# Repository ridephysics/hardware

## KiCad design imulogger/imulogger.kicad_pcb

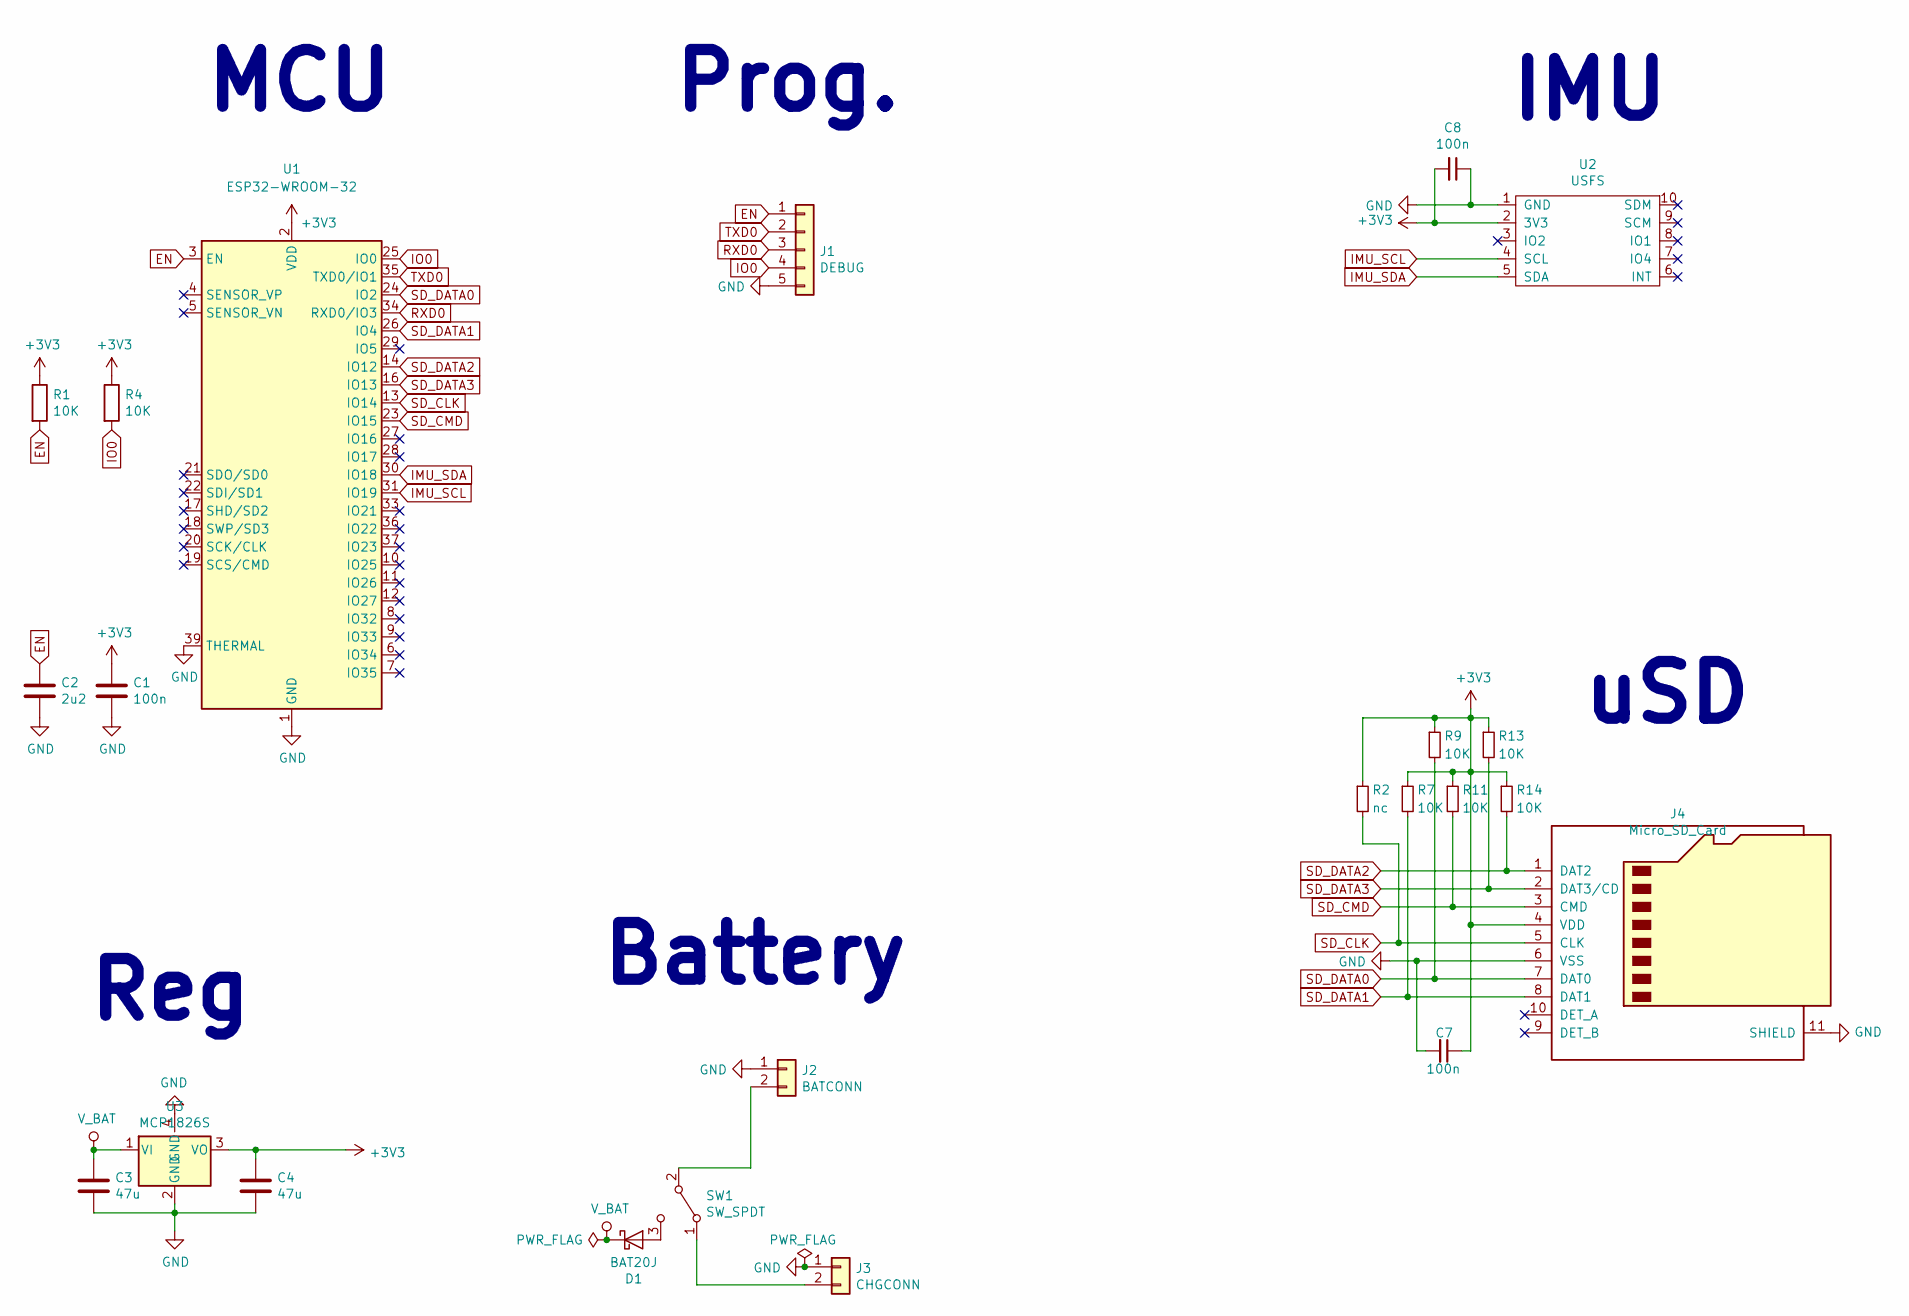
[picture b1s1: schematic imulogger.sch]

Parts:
C1, C7, C8: 100n; C_0805_2012Metric_Pad1.15x1.40mm_HandSolder
C2: 2u2; C_0805_2012Metric_Pad1.15x1.40mm_HandSolder
C3, C4: 47u; C_0805_2012Metric_Pad1.15x1.40mm_HandSolder
D1: BAT20J; D_SOD-323
J1: DEBUG; PinHeader_1x05_P2.54mm_Vertical
J2: BATCONN; PinHeader_1x02_P2.54mm_Vertical
J3: CHGCONN; JST_PH_S2B-PH-K_1x02_P2.00mm_Horizontal
J4: Micro_SD_Card; microSD_HC_Hirose_DM3D-SF
R1, R4, R7, R9, R11, R13, R14: 10K; R_0805_2012Metric_Pad1.15x1.40mm_HandSolder
R2: nc; R_0805_2012Metric_Pad1.15x1.40mm_HandSolder
SW1: SW_SPDT; SK-3296S-01-L3
U1: ESP32-WROOM-32
U2: USFS
U3: MCP1826S; SOT-223

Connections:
+3V3: C1.1, C4.1, C7.1, C8.2, J4.4 (VDD), R1.1, R2.1, R4.1, R7.1, R9.1, R11.1, R13.1, R14.1, U1.2 (VDD), U2.2 (3V3), U3.3 (VO)
EN: C2.1, J1.1, R1.2, U1.3 (EN)
GND: C1.2, C2.2, C3.2, C4.2, C7.2, C8.1, J1.5, J2.1, J3.1, J4.6 (VSS), J4.11 (SHIELD), U1.1 (GND), U1.15 (GND), U1.38 (GND), U1.39 (THERMAL), U2.1 (GND), U3.2 (GND), U3.4 (GND)
IMU_SCL: U1.31 (IO19), U2.4 (SCL)
IMU_SDA: U1.30 (IO18), U2.5 (SDA)
IO0: J1.4, R4.2, U1.25 (IO0)
unnamed: D1.2 (A), SW1.3 (C)
unnamed: J2.2, SW1.2 (B)
unnamed: J3.2, SW1.1 (A)
RXD0: J1.3, U1.34 (RXD0/IO3)
SD_CLK: J4.5 (CLK), R2.2, U1.13 (IO14)
SD_CMD: J4.3 (CMD), R11.2, U1.23 (IO15)
SD_DATA0: J4.7 (DAT0), R9.2, U1.24 (IO2)
SD_DATA1: J4.8 (DAT1), R7.2, U1.26 (IO4)
SD_DATA2: J4.1 (DAT2), R14.2, U1.14 (IO12)
SD_DATA3: J4.2 (DAT3/CD), R13.2, U1.16 (IO13)
TXD0: J1.2, U1.35 (TXD0/IO1)
V_BAT: C3.1, D1.1 (K), U3.1 (VI)

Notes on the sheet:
MCU
uSD
IMU
Prog.
Reg
Battery

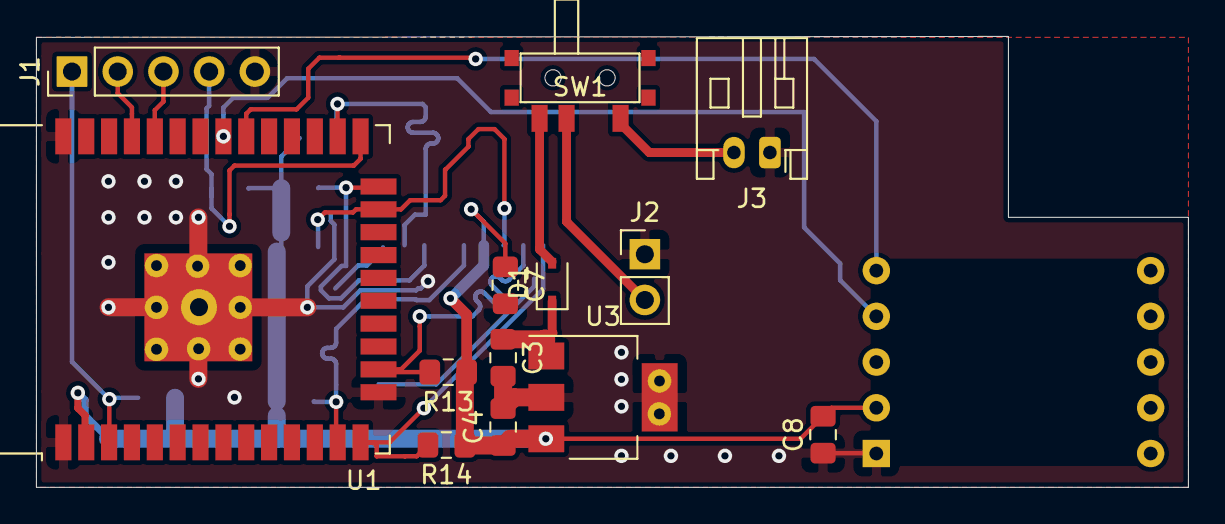
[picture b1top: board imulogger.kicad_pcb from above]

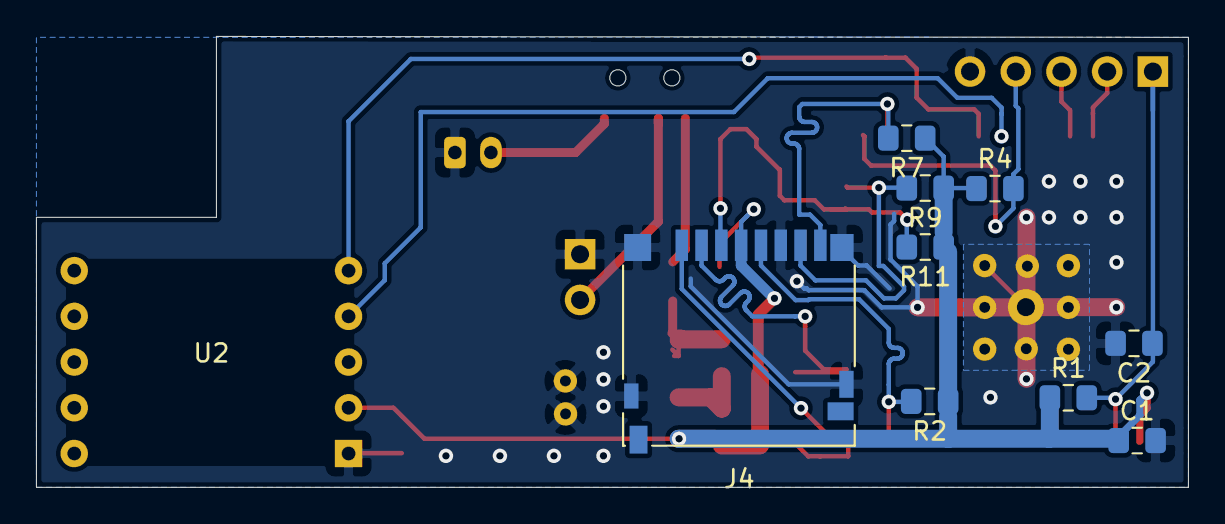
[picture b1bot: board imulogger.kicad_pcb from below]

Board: 2 copper layers, 64.0 x 25.0 mm, 23 parts (10 on the bottom side), 18 nets.

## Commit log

2019-04-17 gitignore: add fp-info-cache
2019-04-17 Initial version
2019-04-18 experiment
2019-04-18 Revert "experiment"
    This reverts commit 6fe68751296b879cc60505c4876b2cc8c070c93c.
2019-04-18 imulogger simply schematic
2019-04-18 imulogger: use 47K pull-ups for sdcard
2019-04-18 imulogger: use 0805 footprints for LDO capacitors
2019-04-18 imulogger: use copy of ESP32 which adds a thermal pin
2019-04-18 imulogger: create copy of esp32 footprint with thermal pad modifications
    this was inspired by the one from olimex
2019-04-18 imulogger: use our custom esp32 footprint
2019-04-20 redesign power supply
    - add battery and charger
    - use LDO with a proper dropout voltage
2019-04-20 Revert "imulogger: use 47K pull-ups for sdcard"
    This reverts commit df5adce347d57e44a57313ac28780a91eea5d007.
    10K is the value recommended by espressif and it's closer to olimex' 2.2k
2019-04-21 imulogger/imulogger-symbols: rename custom power source pins
    otherwise they're all connected to each other
2019-04-21 imulogger: create custom SOT-223 footprint with heat pad optimizations
2019-04-21 imulogger: assign footprints
2019-04-22 use correct pin numbers for thermal holes
2019-04-22 new pcb layout
2019-04-22 pcb optimizations
2019-04-22 pcb: remove excessive vias close to the IMU
2019-05-12 imulogger: pcb: reroute i2c and optimize ground fillings
2019-05-18 imulogger: add battery protection circuit
2019-05-18 imulogger: put connectors on the component side and remove useless track
2019-05-20 imulogger: add SK-3296S-01-L3 footprint
2019-05-20 remove charger and add switch and JST socket
2019-05-20 remove battery protection circuit
    my battery has that already and even if I had one without one
    it'd be easier to buy one and glue it to the battery than soldering
    these small ICs.
2019-05-20 remove 3d model from battery connector
    I'll solder cables instead of using pin headers
2019-05-20 make switch route V_BAT instead of GND
    even though it shouldn't make a difference it's probably better to
    not connect the system load to the charger.
2019-05-20 optimize ground connection
2019-05-21 properly separate i2c and sd using ground plane
    unfortunately I had to remove the 3V3 pin to achieve this
2019-05-21 changes caused by producing gerber and drill files
2019-05-29 add LICENSE
